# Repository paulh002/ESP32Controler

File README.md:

# This repo is archived
Current Arduino version has made this project not fitting anymore in the ESP32 also libraries have updated and are not matching with the code any more.
This repo is only for reference.

# ESP32 USB CAT Controler

A USB remote control for sdrberry or other CAT enabled SDR or VFO
It also for sdrberry controles bandpassfilter and lpf

ToDo:
- add i2c for LPF and BPF

Done:
- USB CAT interface support 

Please add/modify a file credentials.h to the source files for wifi
```
#ifndef _CREDENTIALS_H_			// Prevent double inclusion
#define _CREDENTIALS_H_

#define NUMBR_SSID  2
const char* _ssid[] = {"wifi-ssid1", "wifi-ssid2" };
const char* _password[] = {"password", "password"};

#endif
```

# ESP32 Remote control for raspberry pi

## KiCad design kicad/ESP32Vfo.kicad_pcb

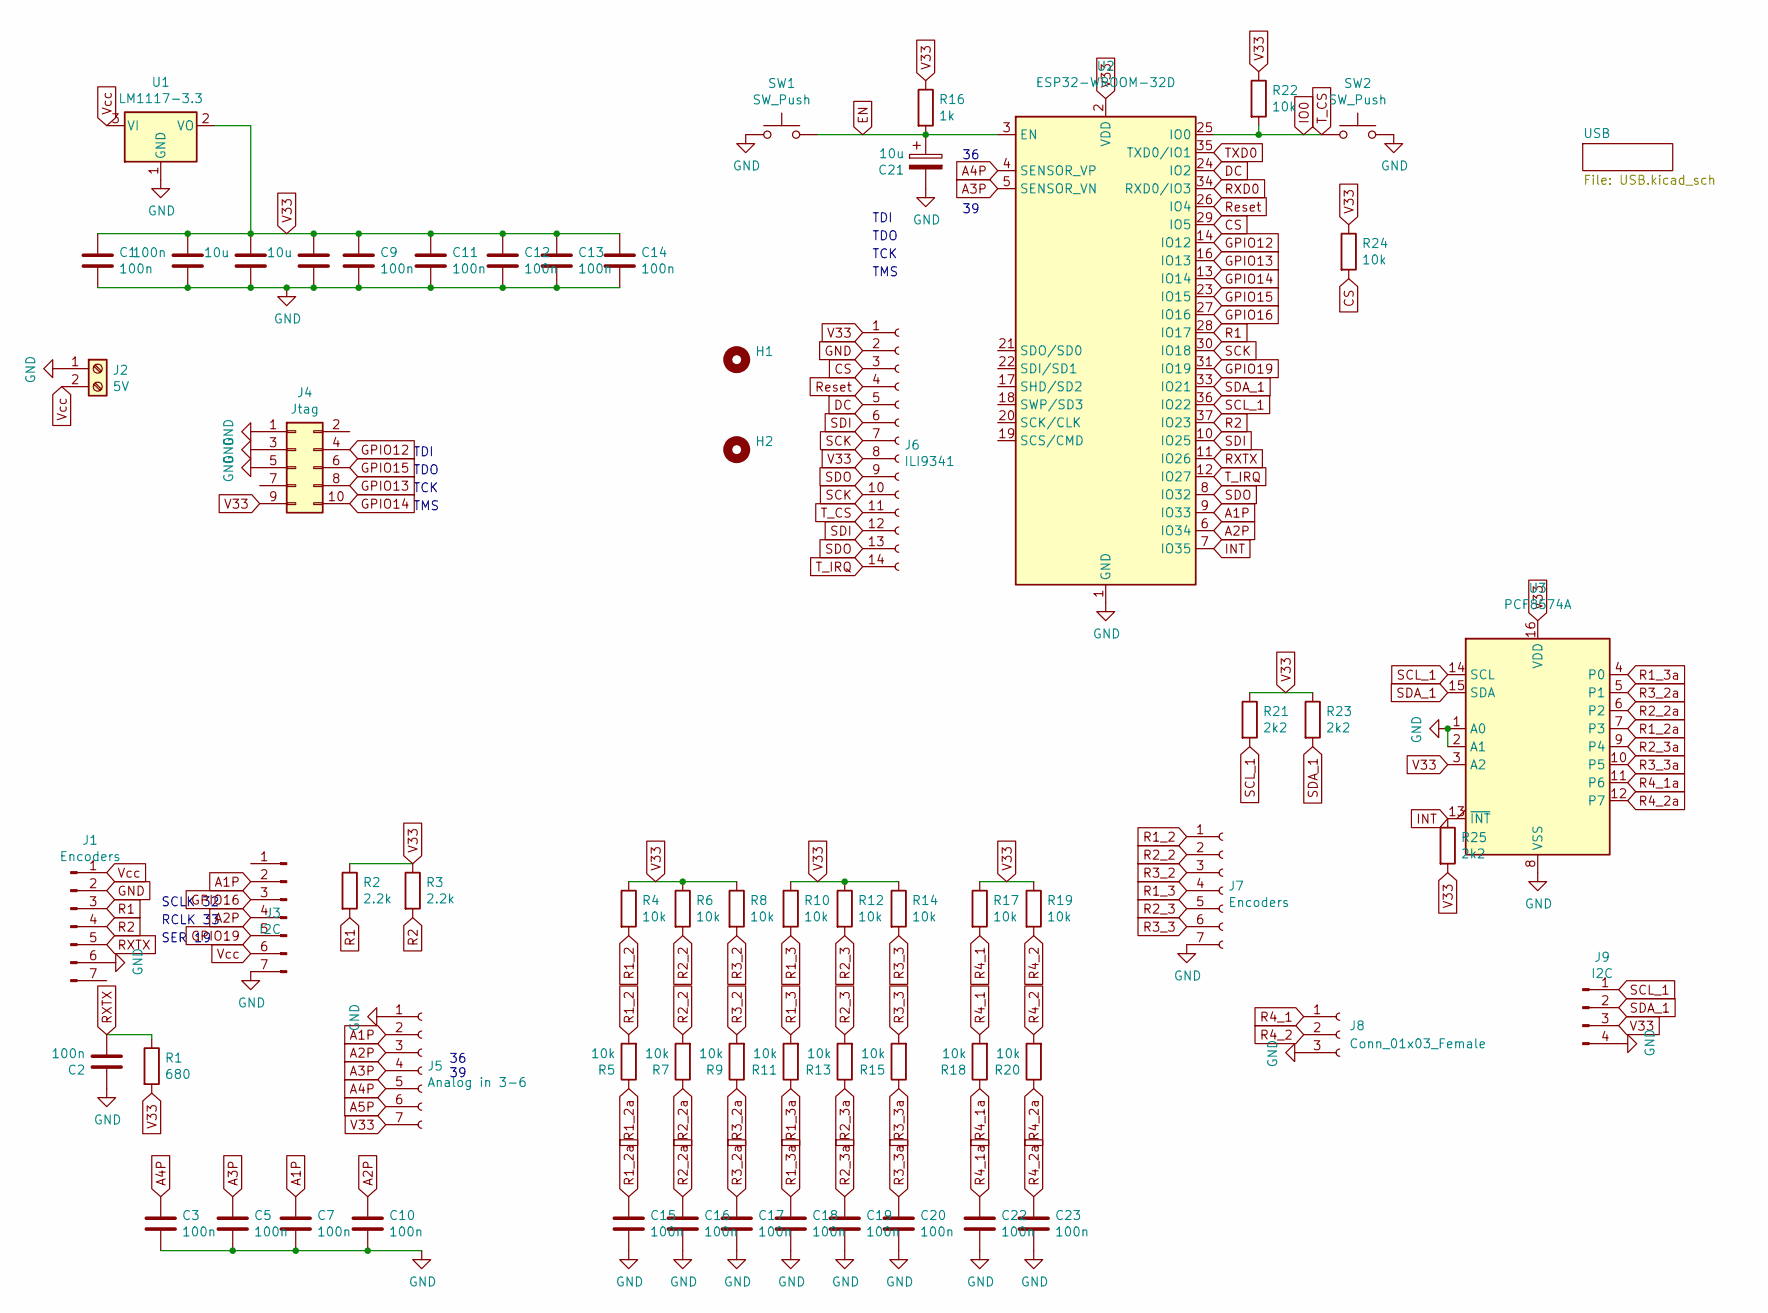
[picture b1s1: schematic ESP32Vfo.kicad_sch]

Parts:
C1, C2, C3, C4, C5, C7, C9, C10, C11, C12, C13, C14, C15, C16, C17, C18, C19, C20, C22, C23: 100n; C_0805_2012Metric
C6, C21: 10u; C_1206_3216Metric_Pad1.42x1.75mm_HandSolder
C8: 10u; C_0805_2012Metric
H1, H2: MountingHole_3.2mm_M3
J1, J7: Encoders; PinSocket_1x07_P2.54mm_Vertical
J2: 5V; TerminalBlock_MetzConnect_Type011_RT05502HBWC_1x02_P5.00mm_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
J3: I2C; PinSocket_1x07_P2.54mm_Vertical
J4: Jtag; PinSocket_2x05_P2.54mm_Vertical
J5: Analog in 3-6; PinSocket_1x07_P2.54mm_Vertical
J6: ILI9341; PinSocket_1x14_P2.54mm_Vertical
J8: Conn_01x03_Female; PinSocket_1x03_P2.54mm_Vertical
J9: I2C; JST_PH_S4B-PH-SM4-TB_1x04-1MP_P2.00mm_Horizontal
R1: 680; R_0805_2012Metric
R2, R3: 2.2k; R_0805_2012Metric
R4, R5, R6, R7, R8, R9, R10, R11, R12, R13, R14, R15, R17, R18, R19, R20, R22, R24: 10k; R_0805_2012Metric
R16: 1k; R_0805_2012Metric
R21, R23, R25: 2k2; R_0805_2012Metric
SW1, SW2: SW_Push; TS-1088R-02526
U1: LM1117-3.3; SOT-223-3_TabPin2
U2: ESP32-WROOM-32D; ESP32-WROOM-32
U3: PCF8574A; SOP-16_7.5x10.4mm_P1.27mm

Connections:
A1P: C7.2, J3.2, J5.2, U2.9 (IO33)
A2P: C10.2, J3.4, J5.3, U2.6 (IO34)
A3P: C5.2, J5.4, U2.5 (SENSOR_VN)
A4P: C3.2, J5.5, U2.4 (SENSOR_VP)
A5P: J5.6
CS: J6.3, R24.2, U2.29 (IO5)
DC: J6.5, U2.24 (IO2)
EN: C21.1, R16.2, SW1.2, U2.3 (EN); also elsewhere on the board
GND: C1.1, C2.2, C3.1, C4.2, C5.1, C6.2, C7.1, C8.2, C9.1, C10.1, C11.1, C12.1, C13.1, C14.1, C15.1, C16.1, C17.1, C18.1, C19.1, C20.1, C21.2, C22.1, C23.1, J1.2, J1.6, J2.1, J3.7, J4.1, J4.3, J4.5, J5.1, J6.2, J7.7, J8.3, J9.4, SW1.1, SW2.2, U1.1 (GND), U2.1 (GND), U2.15 (GND), U2.38 (GND), U2.39 (GND), U3.1 (A0), U3.2 (A1), U3.8 (VSS); also elsewhere on the board
GPIO12: J4.4, U2.14 (IO12)
GPIO13: J4.8, U2.16 (IO13)
GPIO14: J4.10, U2.13 (IO14)
GPIO15: J4.6, U2.23 (IO15)
GPIO16: J3.3, U2.27 (IO16)
GPIO19: J3.5, U2.31 (IO19)
INT: R25.1, U2.7 (IO35), U3.13 (~INT)
IO0: J6.11, R22.2, SW2.1, U2.25 (IO0); also elsewhere on the board
R1: J1.3, R2.2, U2.28 (IO17)
R1_2: J7.1, R4.2, R5.2
R1_2a: C15.2, R5.1, U3.7 (P3)
R1_3: J7.4, R10.2, R11.2
R1_3a: C18.2, R11.1, U3.4 (P0)
R2: J1.4, R3.2, U2.37 (IO23)
R2_2: J7.2, R6.2, R7.2
R2_2a: C16.2, R7.1, U3.6 (P2)
R2_3: J7.5, R12.2, R13.2
R2_3a: C19.2, R13.1, U3.9 (P4)
R3_2: J7.3, R8.2, R9.2
R3_2a: C17.2, R9.1, U3.5 (P1)
R3_3: J7.6, R14.2, R15.2
R3_3a: C20.2, R15.1, U3.10 (P5)
R4_1: J8.1, R17.2, R18.2
R4_1a: C22.2, R18.1, U3.11 (P6)
R4_2: J8.2, R19.2, R20.2
R4_2a: C23.2, R20.1, U3.12 (P7)
RXD0: U2.34 (RXD0/IO3); also elsewhere on the board
RXTX: C2.1, J1.5, R1.1, U2.11 (IO26)
Reset: J6.4, U2.26 (IO4)
SCK: J6.7, J6.10, U2.30 (IO18)
SCL_1: J9.1, R21.2, U2.36 (IO22), U3.14 (SCL)
SDA_1: J9.2, R23.2, U2.33 (IO21), U3.15 (SDA)
SDI: J6.6, J6.12, U2.10 (IO25)
SDO: J6.9, J6.13, U2.8 (IO32)
TXD0: U2.35 (TXD0/IO1); also elsewhere on the board
T_IRQ: J6.14, U2.12 (IO27)
V33: C1.2, C4.1, C6.1, C8.1, C9.2, C11.2, C12.2, C13.2, C14.2, J4.9, J5.7, J6.1, J6.8, J9.3, R1.2, R2.1, R3.1, R4.1, R6.1, R8.1, R10.1, R12.1, R14.1, R16.1, R17.1, R19.1, R21.1, R22.1, R23.1, R24.1, R25.2, U1.2 (VO), U2.2 (VDD), U3.3 (A2), U3.16 (VDD); also elsewhere on the board
Vcc: J1.1, J2.2, J3.6, U1.3 (VI); also elsewhere on the board

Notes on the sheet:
TDI
TMS
TCK
TDO
SER 19
SCLK 32
RCLK 33
36 39

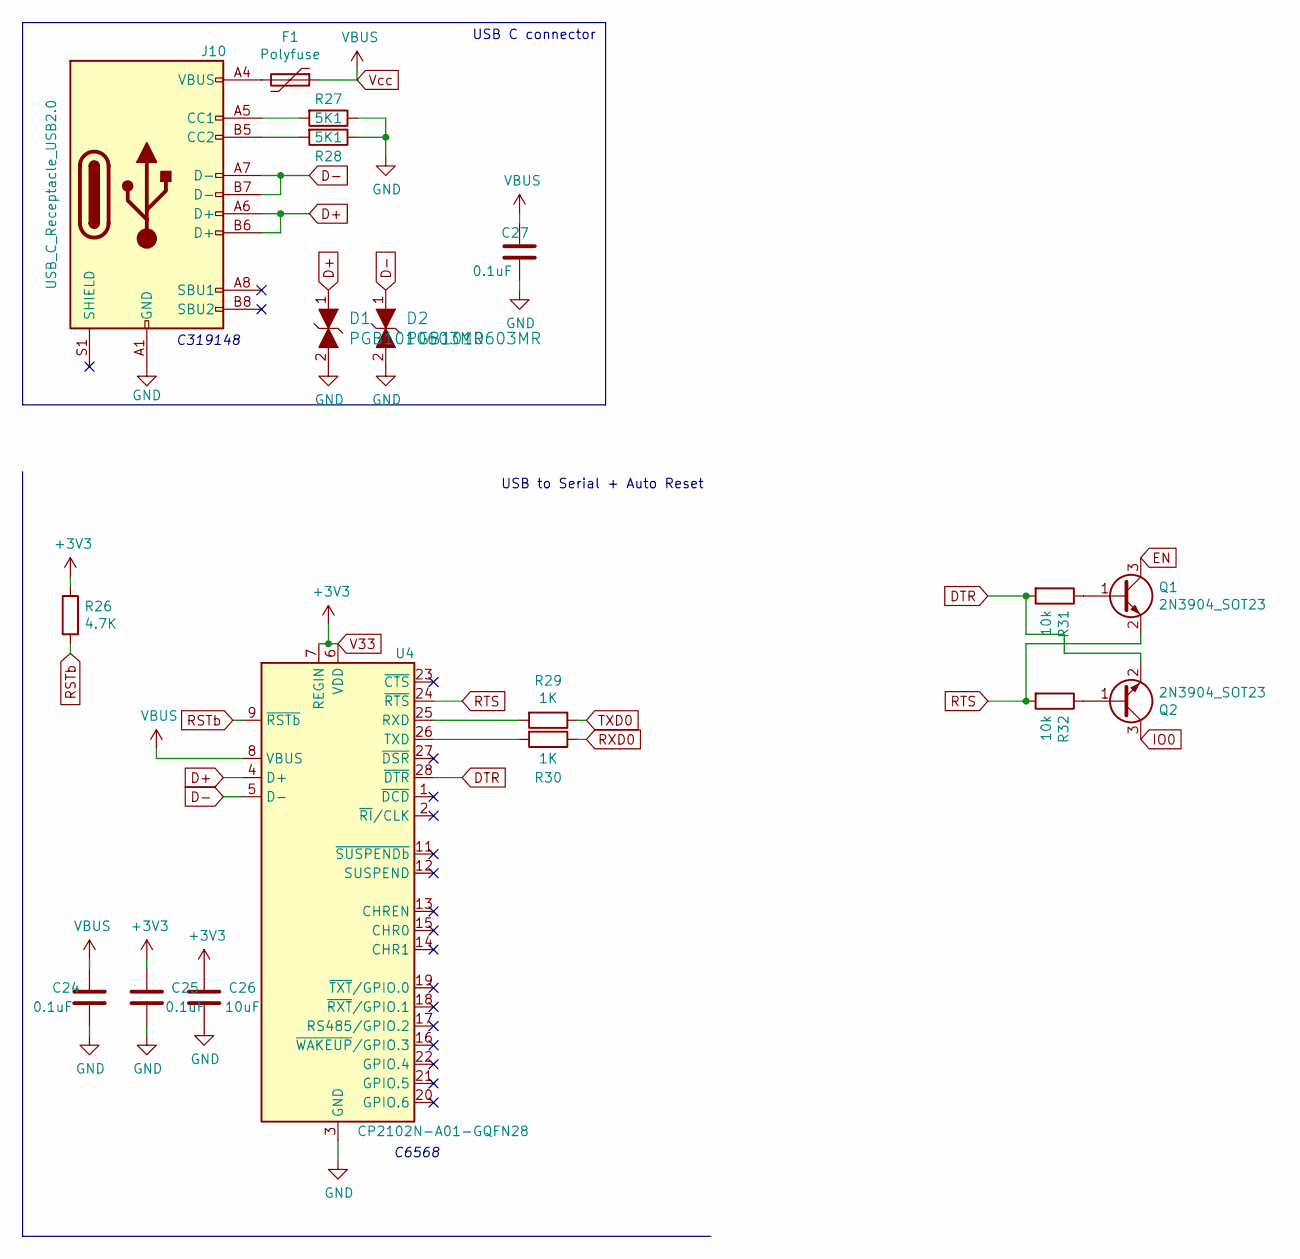
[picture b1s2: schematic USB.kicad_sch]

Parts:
C24, C25, C27: 0.1uF; C_0805_2012Metric
C26: 10uF; C_0805_2012Metric
D1, D2: PGB1010603MR; 0603; MPN PGB1010603MR; Digi-Key_PN F2594CT-ND
F1: Polyfuse; Fuse_0805_2012Metric
J10: USB_C_Receptacle_USB2.0; USB_C_Receptacle_XKB_U262-16XN-4BVC11
Q1, Q2: 2N3904_SOT23; SOT-23
R26: 4.7K; R_0805_2012Metric
R27, R28: 5K1; R_0805_2012Metric
R29, R30: 1K; R_0805_2012Metric
R31, R32: 10k; R_0805_2012Metric
U4: CP2102N-A01-GQFN28; QFN-28-1EP_5x5mm_P0.5mm_EP3.35x3.35mm

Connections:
D+: D1.1, J10.A6 (D+), J10.B6 (D+), U4.4 (D+)
D-: D2.1, J10.A7 (D-), J10.B7 (D-), U4.5 (D-)
DTR: Q2.2 (E), R31.2, U4.28 (~DTR)
EN: Q1.3 (C); also elsewhere on the board
GND: C24.2, C25.2, C26.2, C27.2, D1.2, D2.2, J10.A1 (GND), J10.A12 (GND), J10.B1 (GND), J10.B12 (GND), R27.1, R28.1, U4.3 (GND), U4.29 (GND); also elsewhere on the board
IO0: Q2.3 (C); also elsewhere on the board
unnamed: F1.2, J10.A4 (VBUS), J10.A9 (VBUS), J10.B4 (VBUS), J10.B9 (VBUS)
unnamed: J10.A5 (CC1), R27.2
unnamed: J10.B5 (CC2), R28.2
unnamed: Q1.1 (B), R31.1
unnamed: Q2.1 (B), R32.1
unnamed: R29.2, U4.25 (RXD)
unnamed: R30.2, U4.26 (TXD)
RSTb: R26.2, U4.9 (~RSTb)
RTS: Q1.2 (E), R32.2, U4.24 (~RTS)
RXD0: R30.1; also elsewhere on the board
TXD0: R29.1; also elsewhere on the board
V33: C25.1, C26.1, R26.1, U4.6 (VDD), U4.7 (REGIN); also elsewhere on the board
Vcc: C24.1, C27.1, F1.1, U4.8 (VBUS); also elsewhere on the board

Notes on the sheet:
USB C connector
USB to Serial + Auto Reset
C319148
C6568

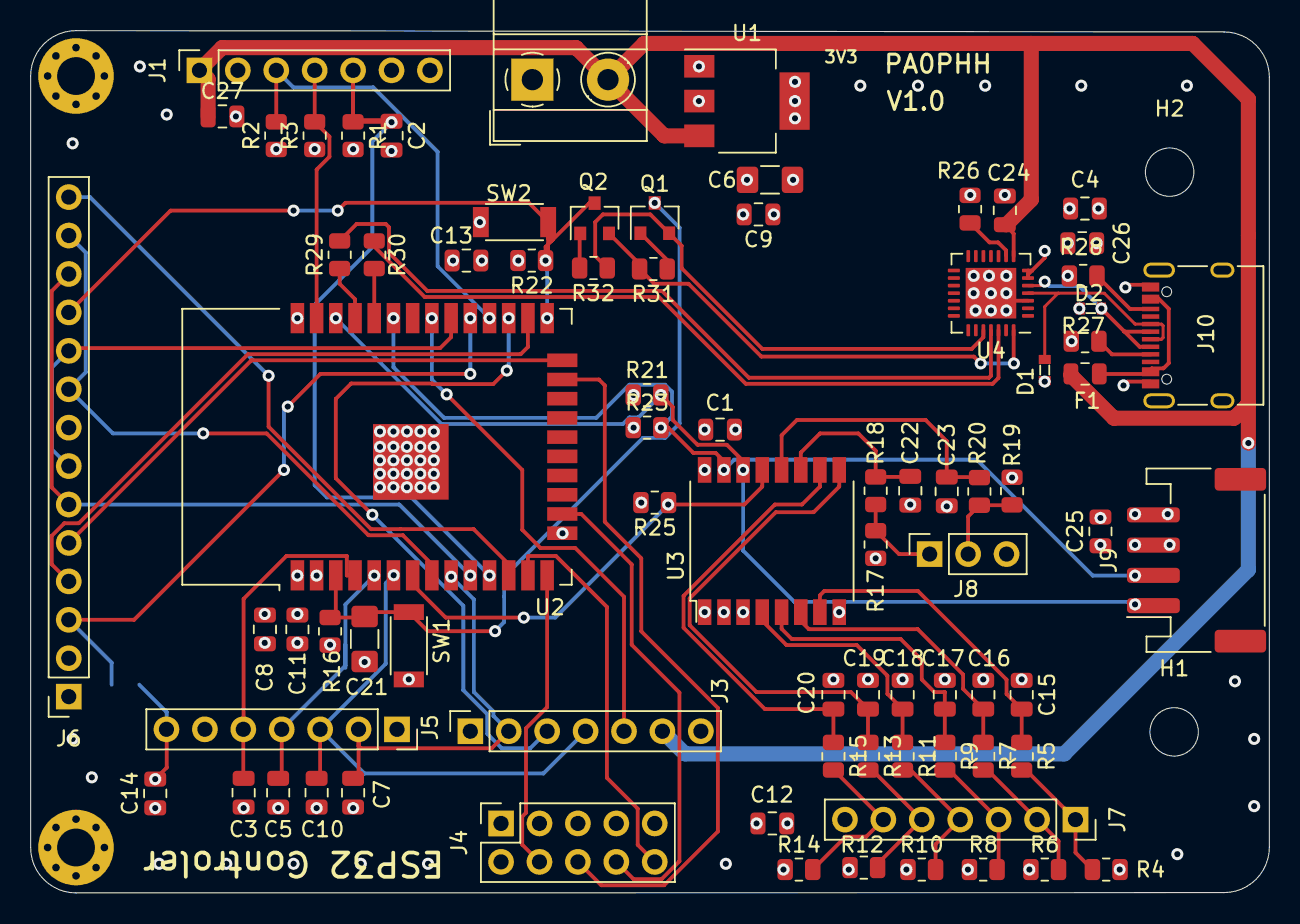
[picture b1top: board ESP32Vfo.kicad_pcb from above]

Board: 4 copper layers, 81.9 x 57.0 mm, 84 parts (1 on the bottom side), 58 nets.

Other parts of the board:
H1#2, H2#2: MountingHole_3.2mm_M3

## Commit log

2021-10-05 Add project files.
2022-10-26 pcf8574 encoders
2022-12-12 New version ESPControler
2023-03-05 add tx switch
2023-03-05 update TX switching
2024-03-17 update pictures
2024-05-03 add kicad files
2025-04-10 readme
2025-04-10 add file
2025-05-18 Archive
